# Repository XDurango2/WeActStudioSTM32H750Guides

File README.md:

# WeActStudio MiniSTM32H7xx – User Guides & Examples

This repository contains a collection of guides and documentation for using the **WeActStudio MiniSTM32H7xx** board, including:

- Flashing the OpenMV firmware  
- Using the board with Arduino IDE  
- Driving the WeActStudio ST7735 display under OpenMV  
- Example scripts and helper files

These guides are intended to simplify development for users working with the STM32H7-based WeActStudio boards.

---

## Included Guides

### 1. Flashing OpenMV Firmware  
Learn how to download the SDK, locate the OpenMV firmware, put the board into DFU mode, and flash the `openmv.bin` file using the WeActStudio download tool.

**Guide:** [`Flashing OpenMV Firmware(Windows)`](Guides-EN/Windows/OpenMV_firmware_flash.md)
**Guide:** [`Flashing OpenMV Firmware(Linux)`](Guides-EN/Linux/OpenMV_firmware_flash.md)

---

### 2. Using the Board with Arduino IDE  
Instructions for installing STM32 board support, configuring DFU upload mode, selecting the correct board, and enabling USB CDC Serial.

**Guide:** [`Arduino IDE Setup(Windows)`](Guides-EN/Windows/Arduino_programming.md)
**Guide:** [`Arduino IDE Setup(Linux)`](Guides-EN/Linux/Arduino_programming.md)

---

### 3. Using the WeActStudio Display in OpenMV  
A detailed guide for copying the display driver scripts, using the example project, and troubleshooting incorrect color tabs for ST7735 screens.

 **Guide:** [`Using the Display in OpenMV`](Guides-EN/OpenMV_display_setup_new.md)

---

### 4. Schematics
Oh, this is New!, in this folder is a KiCad Project Based on the WeAct Board. Please This is a **proof of concept** design. It has **not been tested** in any way, shape, or form.  
These files are provided publicly **for demonstration and educational purposes only**.

**Files:** [`KiCad Project`](Schematics/Schematics_STM32H750.md)

##  Requirements

Depending on the part of the repository you use, you may need:

- **WeActStudio MiniSTM32H7xx board**
- **WeActStudio ST7735 display** (80×160, 128×128, or variant)
- **OpenMV IDE**
- **Arduino IDE 2.x**
- **STM32CubeProgrammer**
- USB-C cable capable of data transfer

---

## 🔗 Useful Links

- WeActStudio GitHub: https://github.com/WeActStudio/MiniSTM32H7xx  
- STM32 Arduino Core: https://github.com/stm32duino  
- OpenMV: https://openmv.io  
- STM32CubeProgrammer: https://www.st.com/en/development-tools/stm32cubeprog.html  

---

## Guías en Español

### 1. Flashear Firmware OpenMV
**Guía:** [`Flashear Firmware OpenMV (Windows)`](Guides-ES/Windows/Flasheo_Firmware_OpenMV.md)
**Guía:** [`Flashear Firmware OpenMV (Linux)`](Guides-ES/Linux/Flasheo_Firmware_OpenMV.md)

---

### 2. Programar con Arduino IDE
**Guía:** [`Configuración Arduino IDE (Windows)`](Guides-ES/Windows/Arduino_IDE_configuracion.md)
**Guía:** [`Configuración Arduino IDE (Linux)`](Guides-ES/Linux/Arduino_IDE_configuracion.md)

---

### 3. Usar el Display en OpenMV
**Guía:** [`Uso del Display en OpenMV`](Guides-ES/Uso_Display_OpenMV_nuevo.md)

---

## Contributing

Pull requests for improving documentation, providing code examples, or adding troubleshooting information are welcome.

---

##  Support

If this repository helps you, consider starring the repo to support its development.

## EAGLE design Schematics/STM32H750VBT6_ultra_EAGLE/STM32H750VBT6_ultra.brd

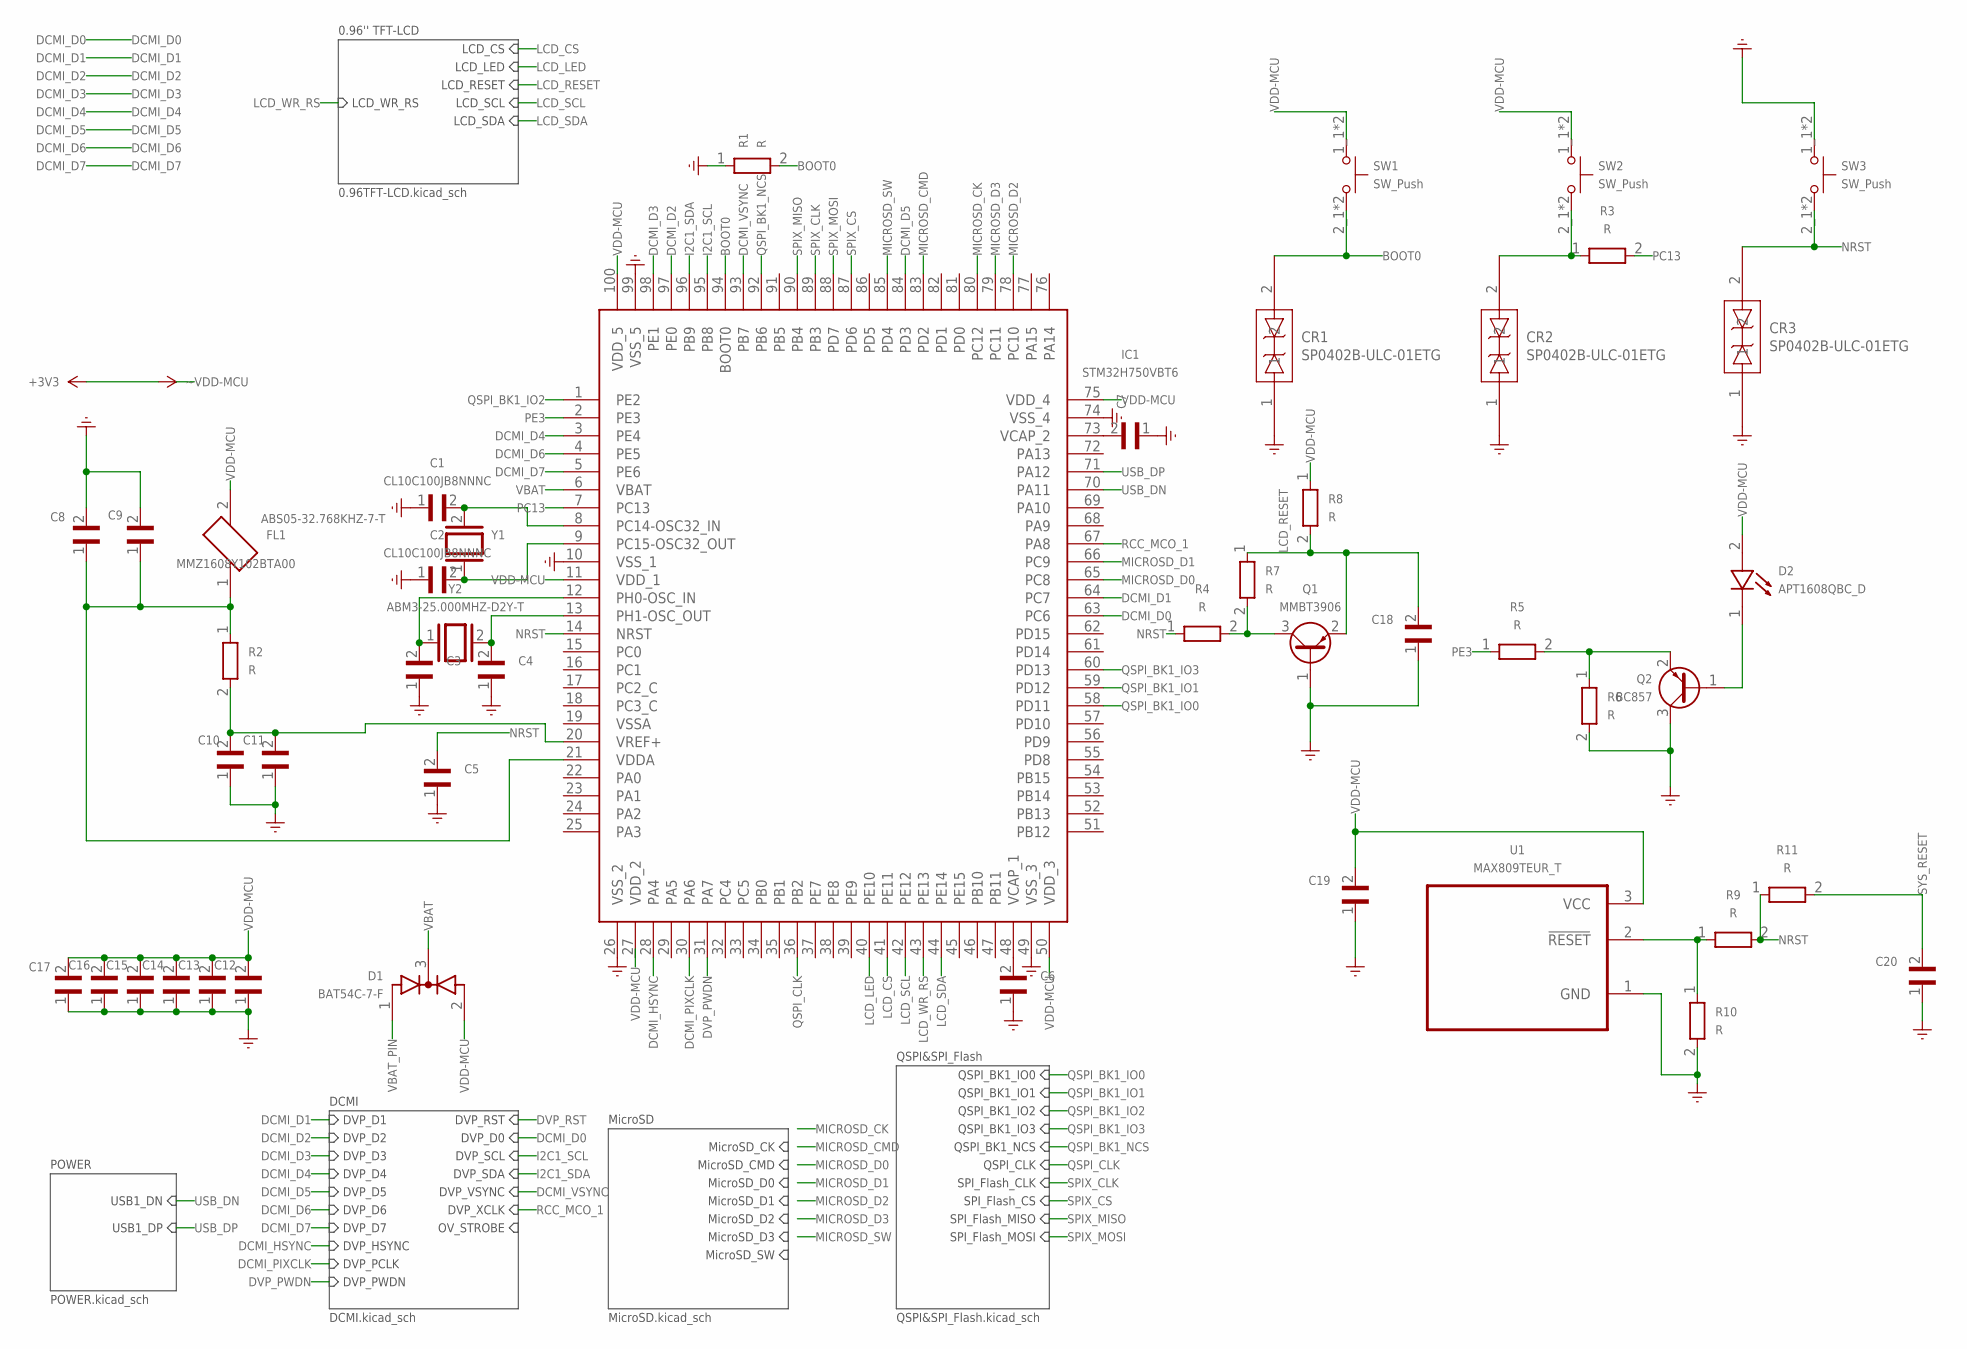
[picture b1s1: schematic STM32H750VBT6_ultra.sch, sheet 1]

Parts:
C1, C2, C3, C4, C5, C6, C7, C8, C9, C10, C11, C12, C13, C14, C15, C16, C17, C19, C20: CL10C100JB8NNNC; CAPACITOR_SMD_C_0201_0603METRIC
C18: CL10C100JB8NNNC; CAPACITOR_SMD_C_0201_0603METRIC_V1
CR1, CR2, CR3: SP0402B-ULC-01ETG; FOOTPRINTS_SP0402_LTF_V1
D1: BAT54C-7-F; PACKAGE_TO_SOT_SMD_SOT-23_HANDSOLDERING; PARTREV 34-2
D2: APT1608QBC_D; LED_SMD_LED_0201_0603METRIC; PARTREV V.20B
FL1: MMZ1608Y102BTA00; INDUCTOR_SMD_L_0603_1608METRIC
IC1: STM32H750VBT6; PACKAGE_QFP_LQFP-100_14X14MM_P0.5MM; MANUFACTURER_PART_NUMBER STM32H750VBT6; MOUSER_PART_NUMBER 511-STM32H750VBT6
Q1: MMBT3906; PACKAGE_TO_SOT_SMD_SOT-23
Q2: BC857; PACKAGE_TO_SOT_SMD_SOT-23
R1, R2, R4, R5, R6, R7, R8, R9, R10, R11: R; RESISTOR_SMD_R_0201_0603METRIC
R3: R; RESISTOR_SMD_R_0201_0603METRIC_V1
SW1, SW2, SW3: SW_Push; BUTTON_SWITCH_SMD_SW_SPST_EVQP7C
U1: MAX809TEUR_T; PACKAGE_TO_SOT_SMD_SOT-23-3
Y1: ABS05-32.768KHZ-7-T; CRYSTAL_CRYSTAL_SMD_3215-2PIN_3.2X1.5MM; PARTREV 11/3/2021
Y2: ABM3-25.000MHZ-D2Y-T; CRYSTAL_CRYSTAL_SMD_3215-2PIN_3.2X1.5MM; PARTREV 4/25/2022

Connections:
BOOT0: CR1.2, IC1.94 (BOOT0), R1.2, SW1.2_1 (2), SW1.2_2 (2)
DCMI_D0: IC1.63 (PC6); also elsewhere on the board
DCMI_D1: IC1.64 (PC7); also elsewhere on the board
DCMI_D2: IC1.97 (PE0); also elsewhere on the board
DCMI_D3: IC1.98 (PE1); also elsewhere on the board
DCMI_D4: IC1.3 (PE4); also elsewhere on the board
DCMI_D5: IC1.84 (PD3); also elsewhere on the board
DCMI_D6: IC1.4 (PE5); also elsewhere on the board
DCMI_D7: IC1.5 (PE6); also elsewhere on the board
DCMI_HSYNC: IC1.28 (PA4); also elsewhere on the board
DCMI_PIXCLK: IC1.30 (PA6); also elsewhere on the board
DCMI_VSYNC: IC1.93 (PB7); also elsewhere on the board
DVP_PWDN: IC1.31 (PA7); also elsewhere on the board
EARTH: C1.1, C2.1, C3.1, C4.1, C5.1, C6.1, C7.1, C8.2, C9.2, C10.1, C11.1, C12.1, C13.1, C14.1, C15.1, C16.1, C17.1, C18.1, C19.1, C20.1, CR1.1, CR2.1, CR3.1, IC1.10 (VSS_1), IC1.26 (VSS_2), IC1.49 (VSS_3), IC1.74 (VSS_4), IC1.99 (VSS_5), Q1.1 (B), Q2.3 (C), R1.1, R6.2, R10.2, SW3.1_1 (1), SW3.1_2 (1), U1.1 (GND); also elsewhere on the board
I2C1_SCL: IC1.95 (PB8); also elsewhere on the board
I2C1_SDA: IC1.96 (PB9); also elsewhere on the board
LCD_CS: IC1.41 (PE11); also elsewhere on the board
LCD_LED: IC1.40 (PE10); also elsewhere on the board
LCD_RESET: C18.2, Q1.2 (E), R7.1, R8.2; also elsewhere on the board
LCD_SCL: IC1.42 (PE12); also elsewhere on the board
LCD_SDA: IC1.44 (PE14); also elsewhere on the board
LCD_WR_RS: IC1.43 (PE13); also elsewhere on the board
MICROSD_CK: IC1.80 (PC12)
MICROSD_CMD: IC1.83 (PD2)
MICROSD_D0: IC1.65 (PC8)
MICROSD_D1: IC1.66 (PC9)
MICROSD_D2: IC1.78 (PC10)
MICROSD_D3: IC1.79 (PC11)
MICROSD_SW: IC1.85 (PD4)
unnamed: Q1.3 (C), R4.2, R7.2
unnamed: C4.2, IC1.13 (PH1-OSC_OUT), Y2.2
unnamed: D2.1, Q2.1 (B)
unnamed: CR2.2, R3.1, SW2.2_1 (2), SW2.2_2 (2)
unnamed: R9.1, R10.1, U1.2 (~RESET)
unnamed: C10.2, C11.2, IC1.20 (VREF+), R2.2
unnamed: Q2.2 (E), R5.2, R6.1
unnamed: C2.2, IC1.9 (PC15-OSC32_OUT), Y1.1
unnamed: C1.2, IC1.8 (PC14-OSC32_IN), Y1.2
unnamed: C8.1, C9.1, FL1.1, IC1.21 (VDDA), R2.1
unnamed: C3.2, IC1.12 (PH0-OSC_IN), Y2.1
unnamed: C7.2, IC1.73 (VCAP_2)
unnamed: C6.2, IC1.48 (VCAP_1)
NRST: C5.2, CR3.2, IC1.14 (NRST), R4.1, R9.2, R11.1, SW3.2_1 (2), SW3.2_2 (2)
PC13: IC1.7 (PC13), R3.2
PE3: IC1.2 (PE3), R5.1
QSPI_BK1_IO0: IC1.58 (PD11); also elsewhere on the board
QSPI_BK1_IO1: IC1.59 (PD12); also elsewhere on the board
QSPI_BK1_IO2: IC1.1 (PE2); also elsewhere on the board
QSPI_BK1_IO3: IC1.60 (PD13); also elsewhere on the board
QSPI_BK1_NCS: IC1.92 (PB6); also elsewhere on the board
QSPI_CLK: IC1.36 (PB2); also elsewhere on the board
RCC_MCO_1: IC1.67 (PA8); also elsewhere on the board
SPIX_CLK: IC1.89 (PB3); also elsewhere on the board
SPIX_CS: IC1.87 (PD6); also elsewhere on the board
SPIX_MISO: IC1.90 (PB4); also elsewhere on the board
SPIX_MOSI: IC1.88 (PD7); also elsewhere on the board
SYS_RESET: C20.2, R11.2
USB_DN: IC1.70 (PA11); also elsewhere on the board
USB_DP: IC1.71 (PA12); also elsewhere on the board
VBAT: D1.3, IC1.6 (VBAT)
VBAT_PIN: D1.1
VDD-MCU: C12.2, C13.2, C14.2, C15.2, C16.2, C17.2, C19.2, D1.2, D2.2, FL1.2, IC1.11 (VDD_1), IC1.27 (VDD_2), IC1.50 (VDD_3), IC1.75 (VDD_4), IC1.100 (VDD_5), R8.1, SW1.1_1 (1), SW1.1_2 (1), SW2.1_1 (1), SW2.1_2 (1), U1.3 (VCC)

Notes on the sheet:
QSPI&SPI_Flash
QSPI&SPI_Flash.kicad_sch
QSPI_BK1_IO0
QSPI_BK1_IO1
QSPI_BK1_IO2
QSPI_BK1_IO3
QSPI_BK1_NCS
QSPI_CLK
SPI_Flash_CLK
SPI_Flash_CS
SPI_Flash_MISO
SPI_Flash_MOSI
MicroSD
MicroSD.kicad_sch
MicroSD_CK
MicroSD_CMD
MicroSD_D0
MicroSD_D1
MicroSD_D2
MicroSD_D3
MicroSD_SW
POWER
POWER.kicad_sch
USB1_DN
USB1_DP
0.96'' TFT-LCD
0.96TFT-LCD.kicad_sch
LCD_CS
LCD_LED
LCD_RESET
LCD_SCL
LCD_SDA
LCD_WR_RS
DCMI
DCMI.kicad_sch
DVP_D0
DVP_D1
DVP_D2
DVP_D3
DVP_D4

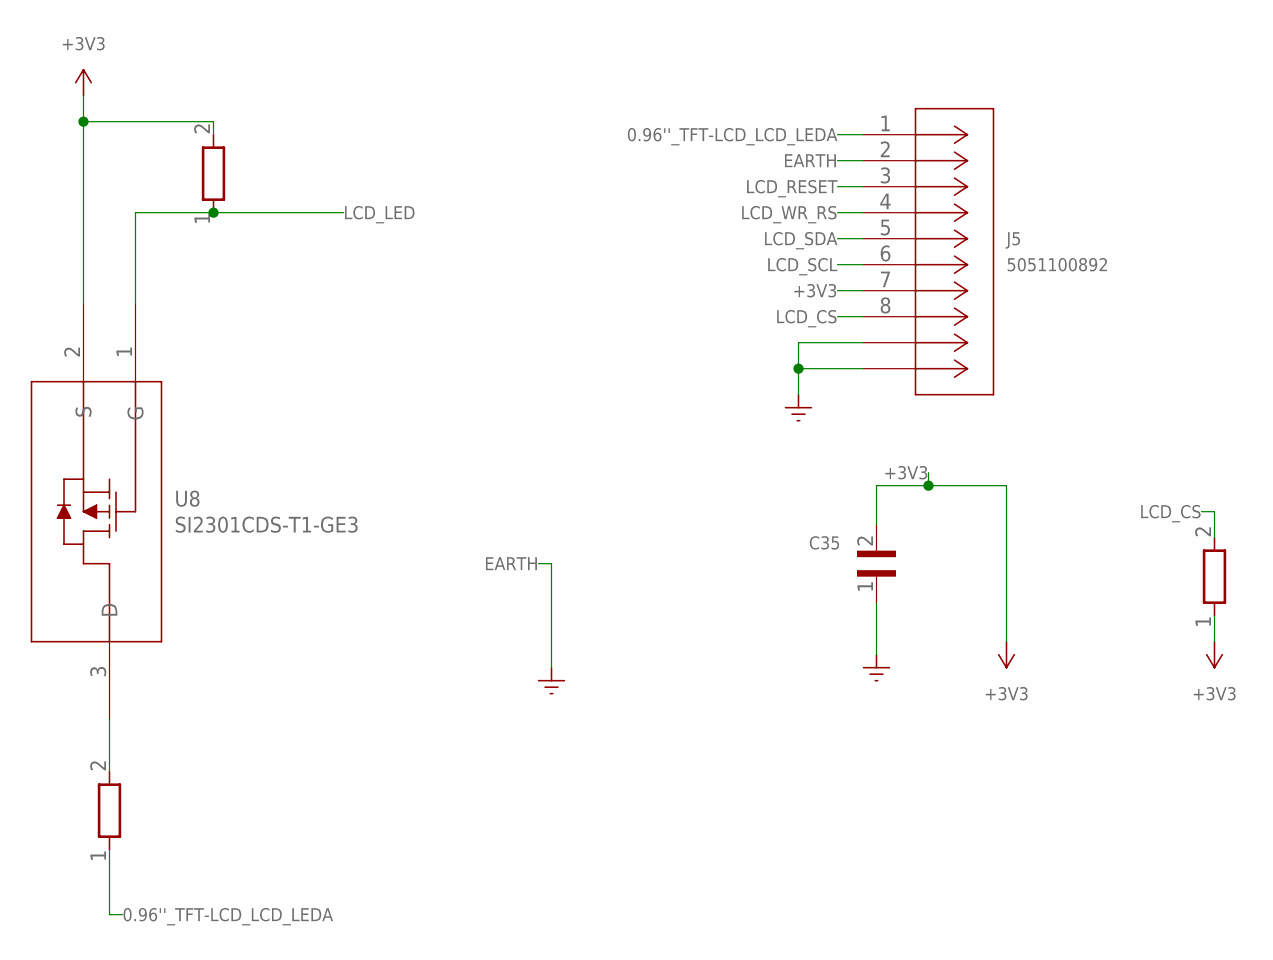
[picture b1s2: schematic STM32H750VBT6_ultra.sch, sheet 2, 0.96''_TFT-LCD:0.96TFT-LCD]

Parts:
C35: CL10C100JB8NNNC; CAPACITOR_SMD_C_0201_0603METRIC
J5: 5051100892; CONNECTOR_FFC-FPC_HIROSE_FH12-8S-0.5SH_1X08-1MP_P0.50MM_HOR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; MANUFACTURER_PART_NUMBER 5051100892
R40, R41, R42: R; RESISTOR_SMD_R_0201_0603METRIC
U8: SI2301CDS-T1-GE3; PACKAGE_TO_SOT_SMD_SOT-23

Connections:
0.96''_TFT-LCD_LCD_LEDA: J5.1, R42.1
+3V3: C35.2, J5.7, R40.1, R41.2, U8.2 (S); also elsewhere on the board
EARTH: C35.1, J5.2; also elsewhere on the board
LCD_CS: J5.8, R40.2; also elsewhere on the board
LCD_LED: R41.1, U8.1 (G); also elsewhere on the board
LCD_RESET: J5.3; also elsewhere on the board
LCD_SCL: J5.6; also elsewhere on the board
LCD_SDA: J5.5; also elsewhere on the board
LCD_WR_RS: J5.4; also elsewhere on the board
unnamed: R42.2, U8.3 (D)

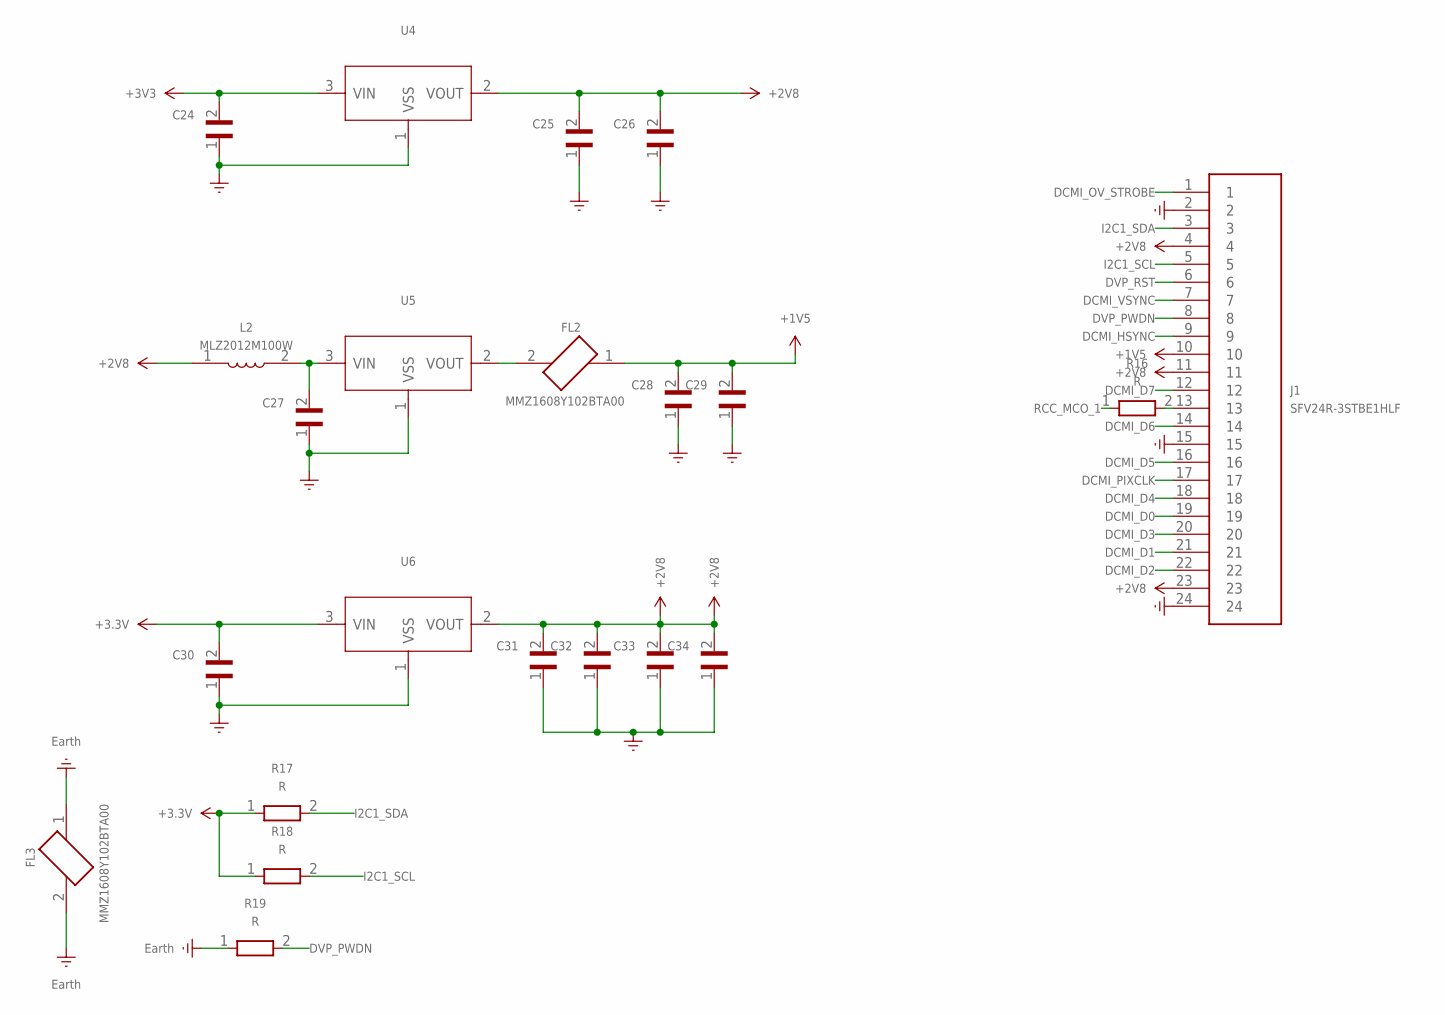
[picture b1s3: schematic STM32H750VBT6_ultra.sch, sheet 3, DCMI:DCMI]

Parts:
C24, C25, C26, C27, C28, C29, C30, C31, C32, C33: CL10C100JB8NNNC; CAPACITOR_SMD_C_0201_0603METRIC
C34: CL10C100JB8NNNC; CAPACITOR_SMD_C_0201_0603METRIC_V1
FL2, FL3: MMZ1608Y102BTA00; INDUCTOR_SMD_L_0603_1608METRIC
J1: SFV24R-3STBE1HLF; AMPHENOL_SFV24R-3STBE1HLF; PARTREV A
L2: MLZ2012M100W; INDUCTOR_SMD_L_0805_2012METRIC
R16, R17, R18, R19: R; RESISTOR_SMD_R_0201_0603METRIC
U4, U5, U6: PMIC-LDO-XC6206P332MR-G_SOT23_; PACKAGE_TO_SOT_SMD_SOT-23-3_V1; MPN XC6206P332MR-G

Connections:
+1V5: C28.2, C29.2, FL2.1, J1.10
+2V8: C25.2, C26.2, C31.2, C32.2, C33.2, C34.2, J1.4, J1.11, J1.23, L2.1, U4.2 (VOUT), U6.2 (VOUT)
+3.3V: C30.2, R17.1, R18.1, U6.3 (VIN); also elsewhere on the board
+3V3: C24.2, U4.3 (VIN); also elsewhere on the board
DCMI_D0: J1.19; also elsewhere on the board
DCMI_D1: J1.21; also elsewhere on the board
DCMI_D2: J1.22; also elsewhere on the board
DCMI_D3: J1.20; also elsewhere on the board
DCMI_D4: J1.18; also elsewhere on the board
DCMI_D5: J1.16; also elsewhere on the board
DCMI_D6: J1.14; also elsewhere on the board
DCMI_D7: J1.12; also elsewhere on the board
DCMI_HSYNC: J1.9; also elsewhere on the board
DCMI_OV_STROBE: J1.1
DCMI_PIXCLK: J1.17; also elsewhere on the board
DCMI_VSYNC: J1.7; also elsewhere on the board
DVP_PWDN: J1.8, R19.2; also elsewhere on the board
DVP_RST: J1.6
EARTH: C24.1, C25.1, C26.1, C27.1, C28.1, C29.1, C30.1, C31.1, C32.1, C33.1, C34.1, FL3.1, FL3.2, J1.2, J1.15, J1.24, R19.1, U4.1 (VSS), U5.1 (VSS), U6.1 (VSS); also elsewhere on the board
I2C1_SCL: J1.5, R18.2; also elsewhere on the board
I2C1_SDA: J1.3, R17.2; also elsewhere on the board
unnamed: C27.2, L2.2, U5.3 (VIN)
unnamed: FL2.2, U5.2 (VOUT)
unnamed: J1.13, R16.2
RCC_MCO_1: R16.1; also elsewhere on the board

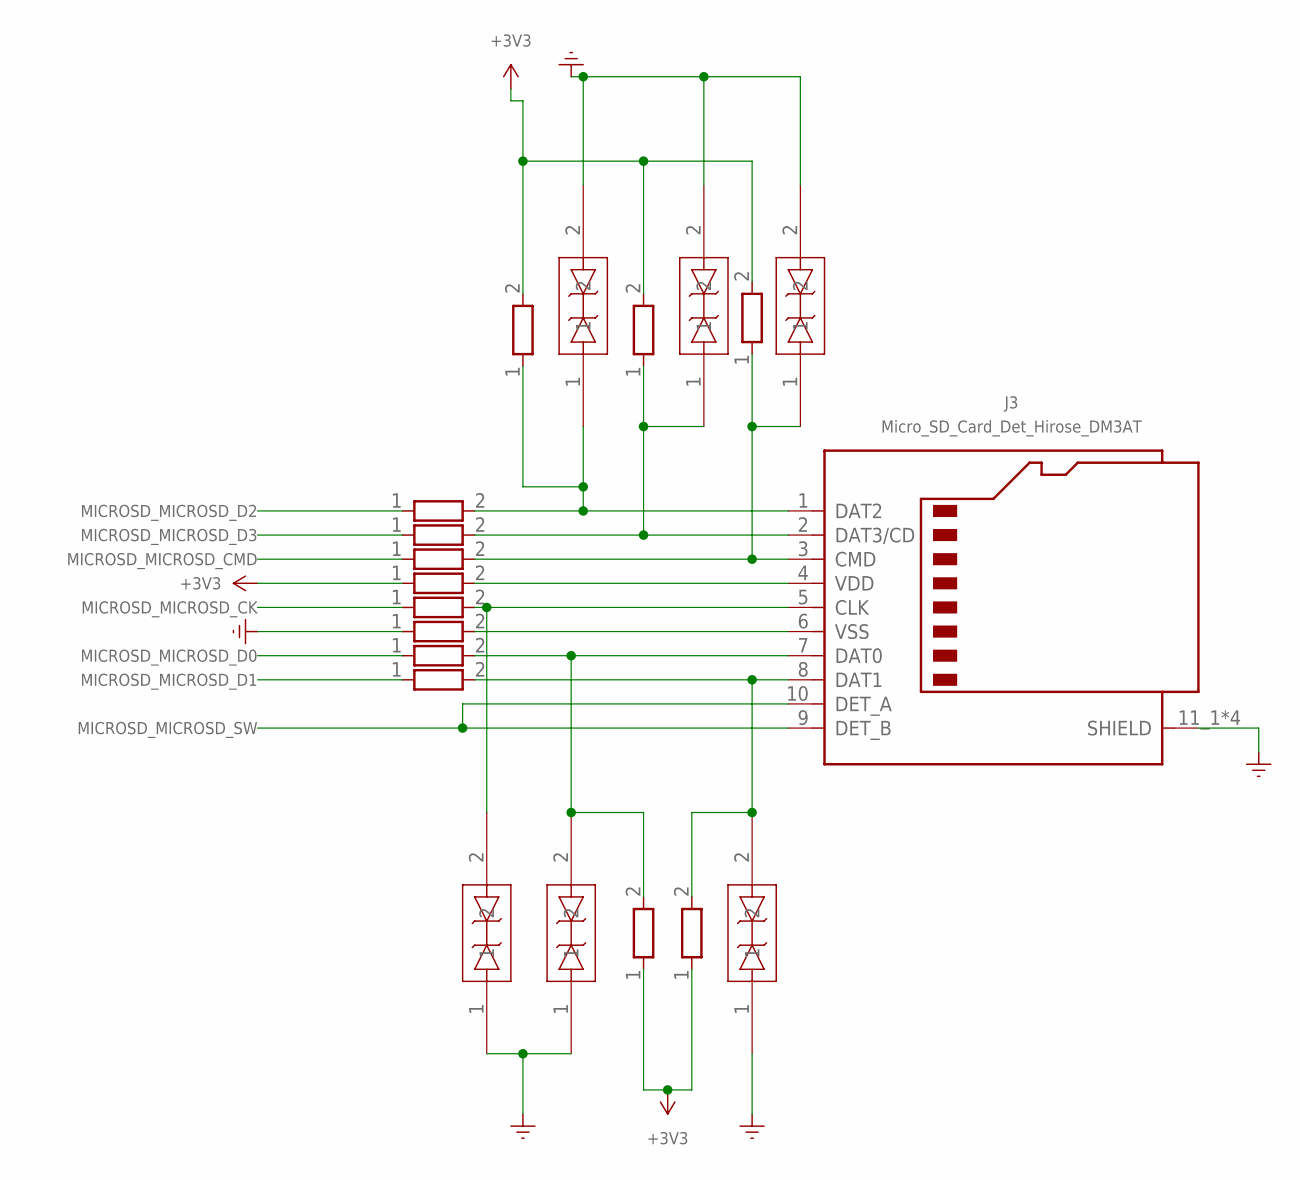
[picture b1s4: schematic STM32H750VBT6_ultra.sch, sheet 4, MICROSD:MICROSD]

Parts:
CR8, CR9, CR10, CR11, CR12, CR13: SP0402B-ULC-01ETG; FOOTPRINTS_SP0402_LTF
J3: Micro_SD_Card_Det_Hirose_DM3AT; CONNECTOR_CARD_MICROSD_HC_HIROSE_DM3AT-SF-PEJM5
R20, R21, R22, R23, R24, R25, R26, R27, R28, R29, R30, R31, R32: R; RESISTOR_SMD_R_0201_0603METRIC

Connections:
+3V3: R23.1, R28.2, R29.2, R30.2, R31.1, R32.1; also elsewhere on the board
EARTH: CR8.2, CR9.2, CR10.2, CR11.1, CR12.1, CR13.1, J3.11_1 (SHIELD), J3.11_2 (SHIELD), J3.11_3 (SHIELD), J3.11_4 (SHIELD), R25.1; also elsewhere on the board
MICROSD_MICROSD_CK: R24.1
MICROSD_MICROSD_CMD: R22.1
MICROSD_MICROSD_D0: R26.1
MICROSD_MICROSD_D1: R27.1
MICROSD_MICROSD_D2: R20.1
MICROSD_MICROSD_D3: R21.1
MICROSD_MICROSD_SW: J3.9 (DET_B), J3.10 (DET_A)
unnamed: J3.4 (VDD), R23.2
unnamed: CR10.1, J3.3 (CMD), R22.2, R30.1
unnamed: CR8.1, J3.1 (DAT2), R20.2, R28.1
unnamed: CR9.1, J3.2 (DAT3/CD), R21.2, R29.1
unnamed: CR12.2, J3.7 (DAT0), R26.2, R31.2
unnamed: CR11.2, J3.5 (CLK), R24.2
unnamed: J3.6 (VSS), R25.2
unnamed: CR13.2, J3.8 (DAT1), R27.2, R32.2

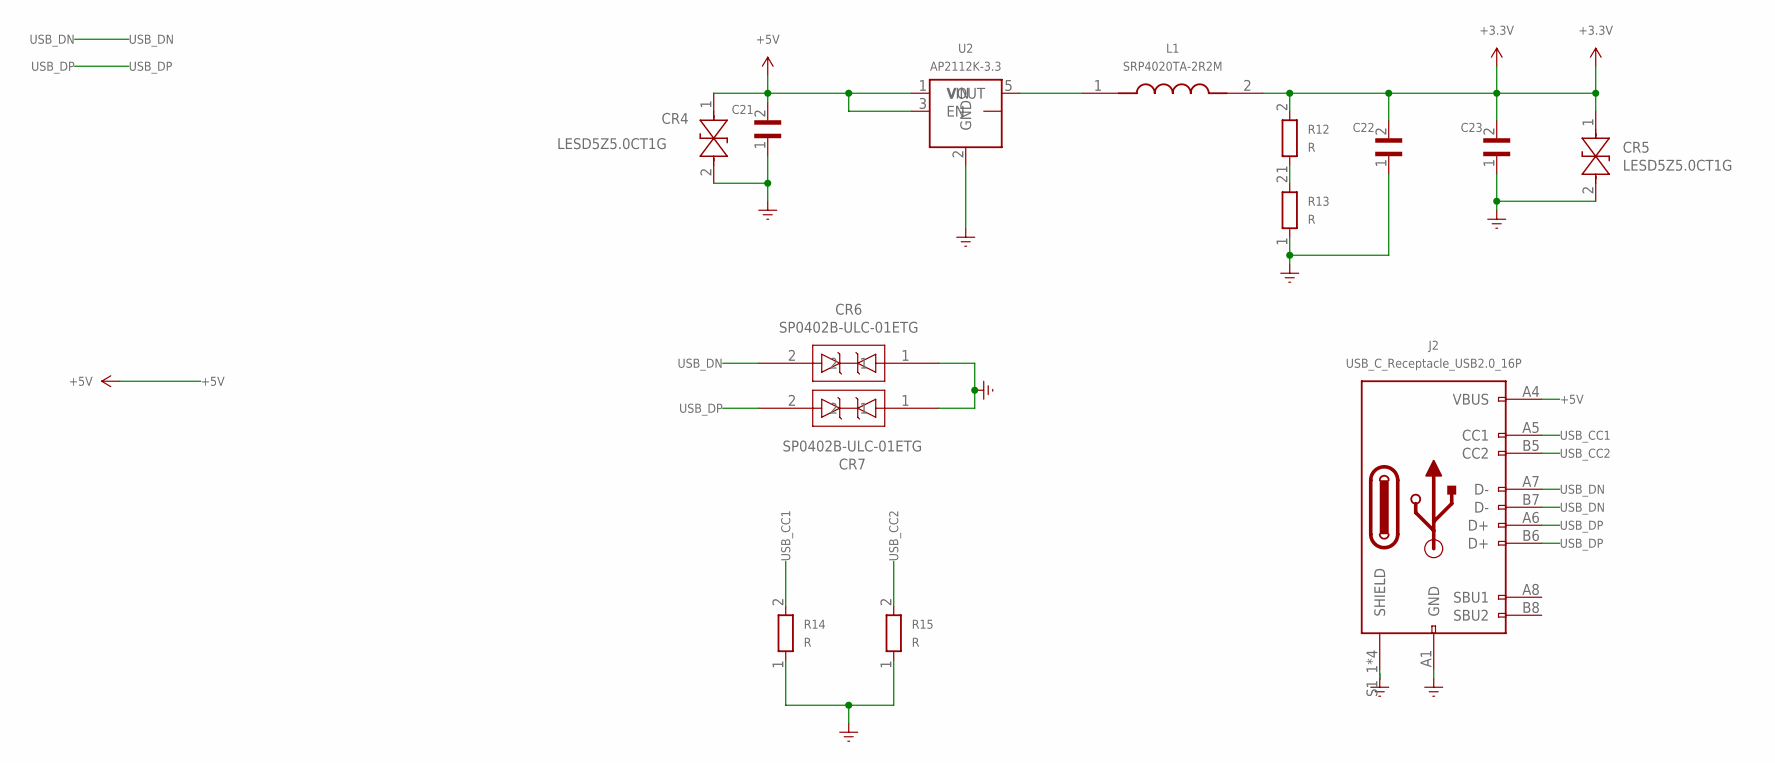
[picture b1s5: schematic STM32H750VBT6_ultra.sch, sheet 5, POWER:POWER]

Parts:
C21, C22, C23: CL10C100JB8NNNC; CAPACITOR_SMD_C_0201_0603METRIC
CR4: LESD5Z5.0CT1G; DIODE_SMD_D_SOD-523_V1
CR5: LESD5Z5.0CT1G; DIODE_SMD_D_SOD-523
CR6, CR7: SP0402B-ULC-01ETG; FOOTPRINTS_SP0402_LTF_V1
J2: USB_C_Receptacle_USB2.0_16P; CONNECTOR_USB_USB_C_RECEPTACLE_GCT_USB4110
L1: SRP4020TA-2R2M; INDUCTOR_SMD_L_COILCRAFT_XXL4020
R12, R13, R14, R15: R; RESISTOR_SMD_R_0201_0603METRIC
U2: AP2112K-3.3; PACKAGE_TO_SOT_SMD_SOT-23-5

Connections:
+3.3V: C22.2, C23.2, CR5.1, L1.2, R12.2; also elsewhere on the board
+5V: C21.2, CR4.1, J2.A4 (VBUS), J2.A9 (VBUS), J2.B4 (VBUS), J2.B9 (VBUS), U2.1 (VIN), U2.3 (EN)
EARTH: C21.1, C22.1, C23.1, CR4.2, CR5.2, CR6.1, CR7.1, J2.A1 (GND), J2.A12 (GND), J2.B1 (GND), J2.B12 (GND), J2.S1_1 (SHIELD), J2.S1_2 (SHIELD), J2.S1_3 (SHIELD), J2.S1_4 (SHIELD), R13.1, R14.1, R15.1, U2.2 (GND); also elsewhere on the board
unnamed: L1.1, U2.5 (VOUT)
unnamed: R12.1, R13.2
USB_CC1: J2.A5 (CC1), R14.2
USB_CC2: J2.B5 (CC2), R15.2
USB_DN: CR6.2, J2.A7 (D-), J2.B7 (D-); also elsewhere on the board
USB_DP: CR7.2, J2.A6 (D+), J2.B6 (D+); also elsewhere on the board

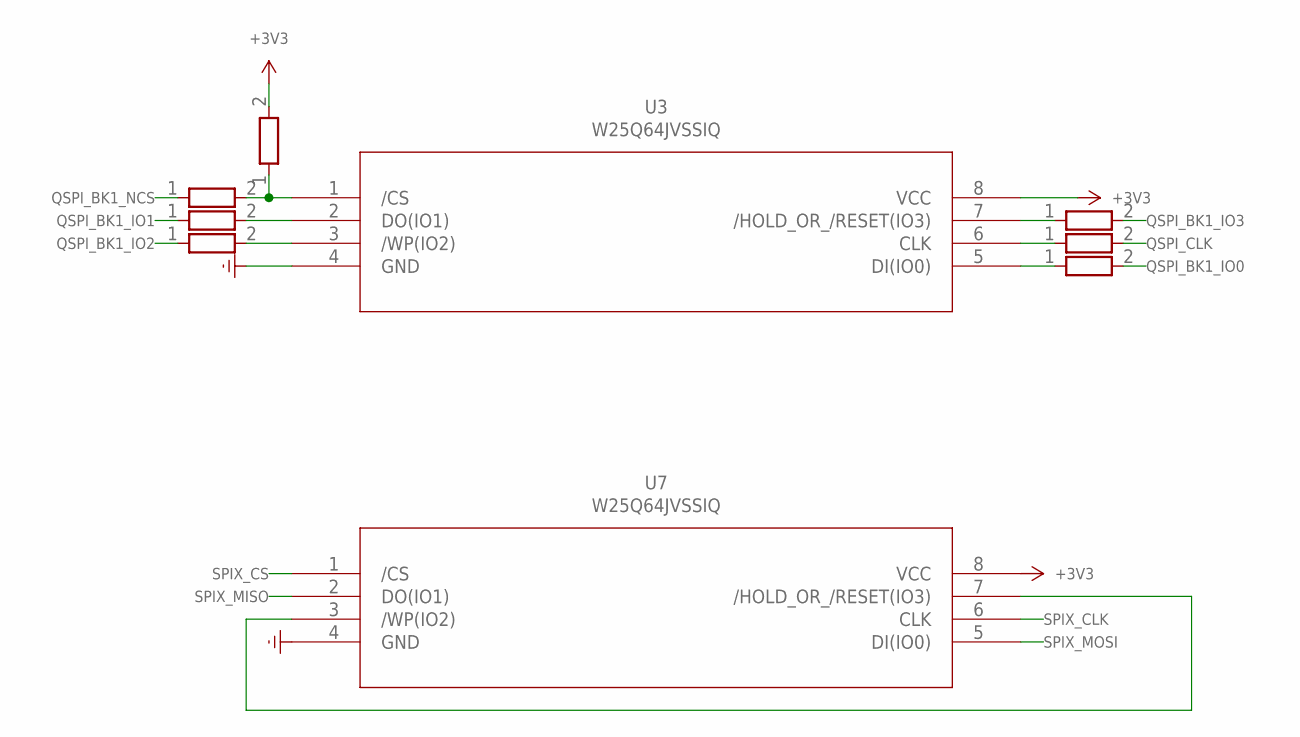
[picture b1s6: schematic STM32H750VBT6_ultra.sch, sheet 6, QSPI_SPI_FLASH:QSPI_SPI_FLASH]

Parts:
R33, R34, R35, R36: R; RESISTOR_SMD_R_0201_0603METRIC_V1
R37, R38, R39: R; RESISTOR_SMD_R_0201_0603METRIC
U3, U7: W25Q64JVSSIQ; PACKAGE_SO_SOIC-8_3.9X4.9MM_P1.27MM

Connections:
+3V3: R39.2, U3.8 (VCC), U7.8 (VCC); also elsewhere on the board
EARTH: U3.4 (GND), U7.4 (GND); also elsewhere on the board
unnamed: U7.3 (/WP(IO2)), U7.7 (/HOLD_OR_/RESET(IO3))
unnamed: R35.2, U3.3 (/WP(IO2))
unnamed: R33.2, R39.1, U3.1 (/CS)
unnamed: R34.2, U3.2 (DO(IO1))
unnamed: R36.1, U3.7 (/HOLD_OR_/RESET(IO3))
unnamed: R38.1, U3.5 (DI(IO0))
unnamed: R37.1, U3.6 (CLK)
QSPI_BK1_IO0: R38.2; also elsewhere on the board
QSPI_BK1_IO1: R34.1; also elsewhere on the board
QSPI_BK1_IO2: R35.1; also elsewhere on the board
QSPI_BK1_IO3: R36.2; also elsewhere on the board
QSPI_BK1_NCS: R33.1; also elsewhere on the board
QSPI_CLK: R37.2; also elsewhere on the board
SPIX_CLK: U7.6 (CLK); also elsewhere on the board
SPIX_CS: U7.1 (/CS); also elsewhere on the board
SPIX_MISO: U7.2 (DO(IO1)); also elsewhere on the board
SPIX_MOSI: U7.5 (DI(IO0)); also elsewhere on the board

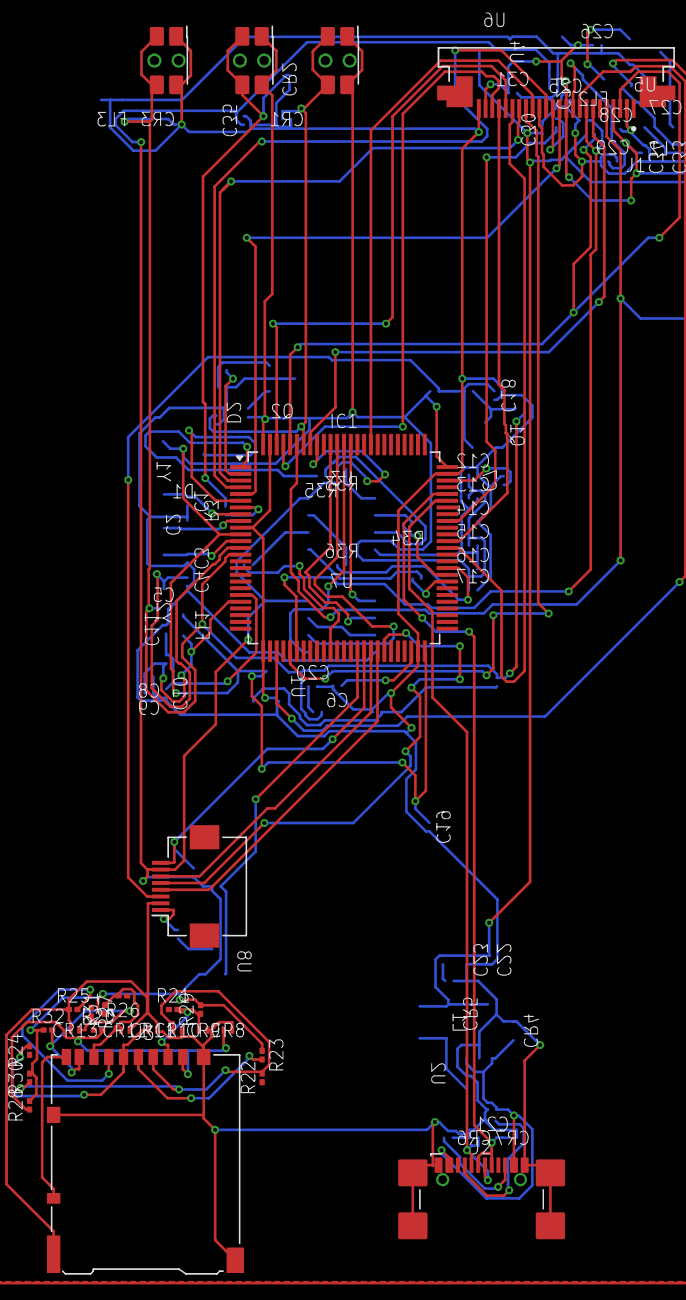
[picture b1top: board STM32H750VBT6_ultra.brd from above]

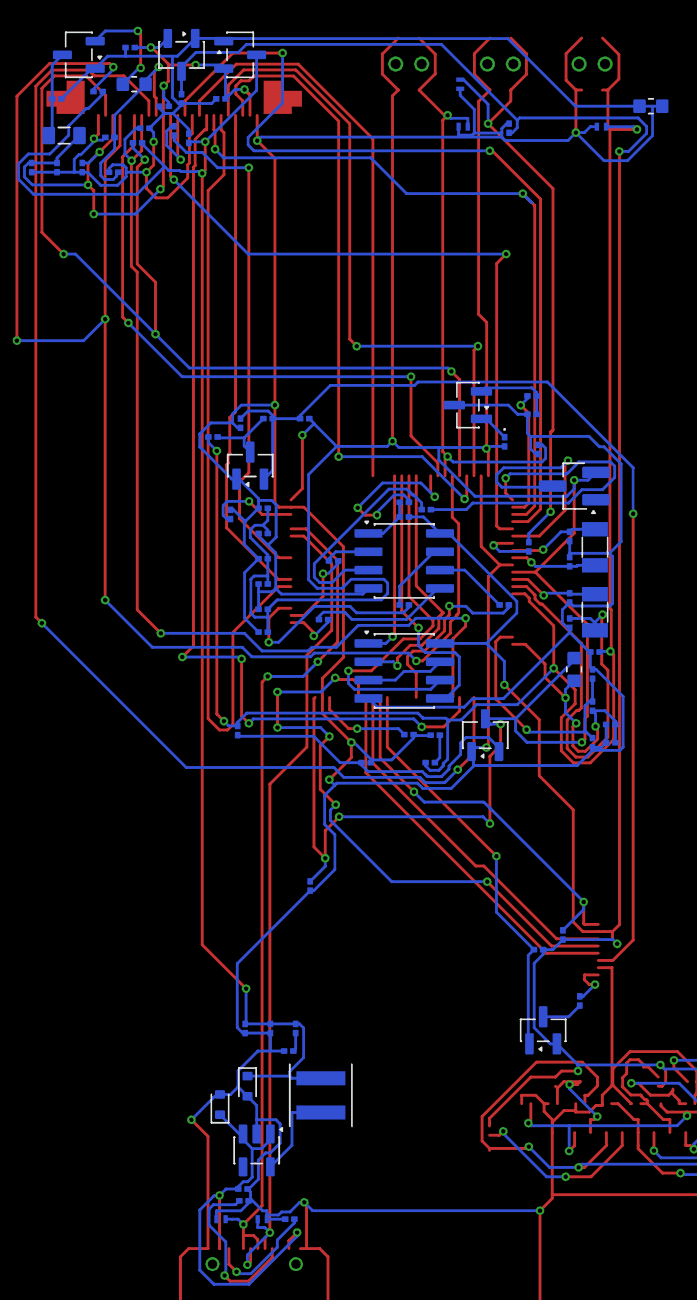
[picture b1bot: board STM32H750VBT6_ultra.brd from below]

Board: 2 copper layers, 117 parts (90 on the bottom side), 84 nets.

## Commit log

2025-11-16 Guides in English Added
2025-11-16 renaming of guides-EN
2025-11-16 README added
    This README provides comprehensive user guides and examples for the WeActStudio MiniSTM32H7xx board, covering topics like firmware flashing, Arduino IDE setup, and display usage.
2025-11-16 Add link to OpenMV firmware flashing guide
2025-11-16 changing guide names in spanish
2025-11-16 Update prerequisites with flashing guide link
    Added link to the OpenMV firmware flashing guide.
2025-11-16 Fix link case sensitivity in OpenMV guide
2025-11-16 Fix link to OpenMV display setup guide
2025-11-16 Update link to OpenMV display guide
2025-11-16 Fix link case sensitivity in README.md
2025-11-16 Fix formatting in OpenMV display setup guide
2025-11-16 Clean up README formatting
    Removed unnecessary lines in the README file.
2025-11-16 Update file path reference in display setup guide
2025-11-18 schematic diagrams
2025-11-18 READMEs added to the schematics
2025-11-19 PCB images
2025-11-26 schematic files and PCBs in Eagle
2026-05-14 agregado de Linux y division de explicaciones por SO
2026-05-14 fix de typos en guia y agregado de guía en inglés
2026-05-14 linux links added
2026-05-14 spanish guides added to the README and linux links added to other guides
2026-05-14 firmware version notes added
2026-05-14 hotfix #1: typos in model names
2026-06-03 Update display guides for firmware version changes and add new examples
2026-06-03 Update OpenMV display setup guide link
